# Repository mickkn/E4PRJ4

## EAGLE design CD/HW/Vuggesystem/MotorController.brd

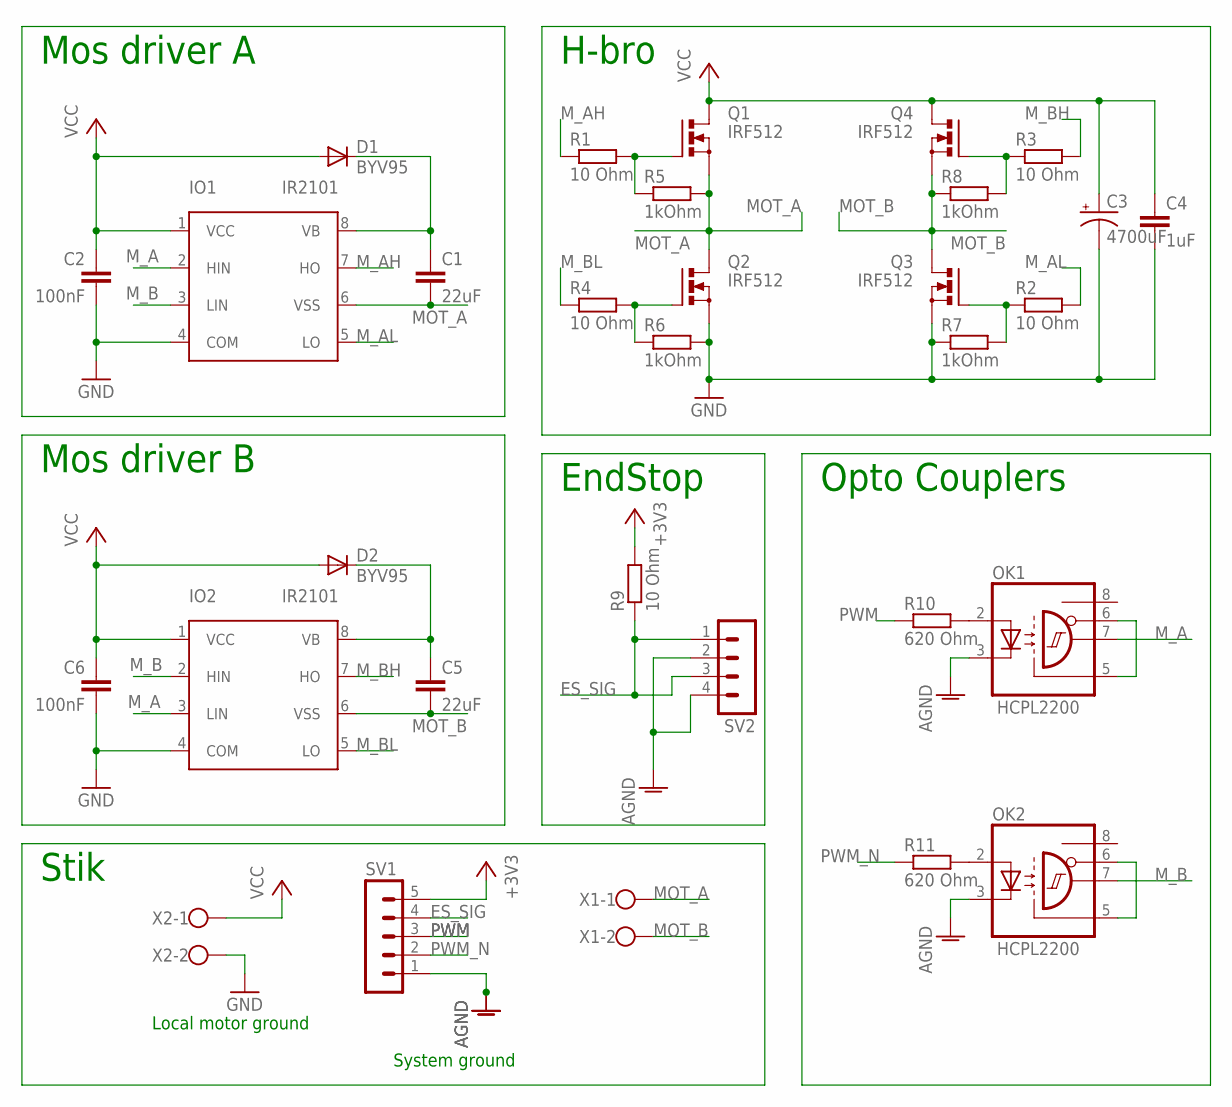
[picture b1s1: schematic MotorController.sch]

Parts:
C1, C5: 22uF; CAP-PTH-5MM
C2, C6: 100nF; CAP-PTH-5MM
C3: 4700uF; CPOL-RADIAL-1000UF-25V
C4: 1uF; CAP-PTH-5MM
D1, D2: BYV95; SOD57-10
IO1, IO2: IR2101; DIL08
OK1, OK2: HCPL2200; DIL08
Q1, Q2, Q3, Q4: IRF512; TO220BV
R1, R2, R3, R4, R9: 10 Ohm; 0207/10
R5, R6, R7, R8: 1kOhm; 0207/10
R10, R11: 620 Ohm; 0207/10
SV1: MA05-1
SV2: MA04-1
X1, X2: W237-102

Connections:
+3V3: R9.2, SV1.5
AGND: OK1.3 (C), OK2.3 (C), SV1.1, SV2.2, SV2.4
ES_SIG: R9.1, SV1.4, SV2.1, SV2.3
GND: C2.2, C3.2 (-), C4.2, C6.2, IO1.4 (COM), IO2.4 (COM), Q2.S, Q3.S, R6.2, R7.1, X2.2
MOT_A: C1.2, IO1.6 (VSS), Q1.S, Q2.D, R5.2, X1.1
MOT_B: C5.2, IO2.6 (VSS), Q3.D, Q4.S, R8.1, X1.2
M_A: IO1.2 (HIN), IO2.3 (LIN), OK1.7 (VO)
M_AH: IO1.7 (HO), R1.1
M_AL: IO1.5 (LO), R2.2
M_B: IO1.3 (LIN), IO2.2 (HIN), OK2.7 (VO)
M_BH: IO2.7 (HO), R3.2
M_BL: IO2.5 (LO), R4.1
unnamed: C5.1, D2.C, IO2.8 (VB)
unnamed: Q1.G, R1.2, R5.1
unnamed: Q2.G, R4.2, R6.1
unnamed: Q4.G, R3.1, R8.2
unnamed: Q3.G, R2.1, R7.2
unnamed: C1.1, D1.C, IO1.8 (VB)
unnamed: OK1.2 (A), R10.2
unnamed: OK2.2 (A), R11.2
unnamed: OK2.5 (GND), OK2.6 (VE)
unnamed: OK1.5 (GND), OK1.6 (VE)
PWM: R10.1, SV1.3
PWM_N: R11.1, SV1.2
VCC: C2.1, C3.1 (+), C4.1, C6.1, D1.A, D2.A, IO1.1 (VCC), IO2.1 (VCC), Q1.D, Q4.D, X2.1

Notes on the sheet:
H-bro
Mos driver A
Mos driver B
Stik
EndStop
System ground
Local motor ground
Opto Couplers

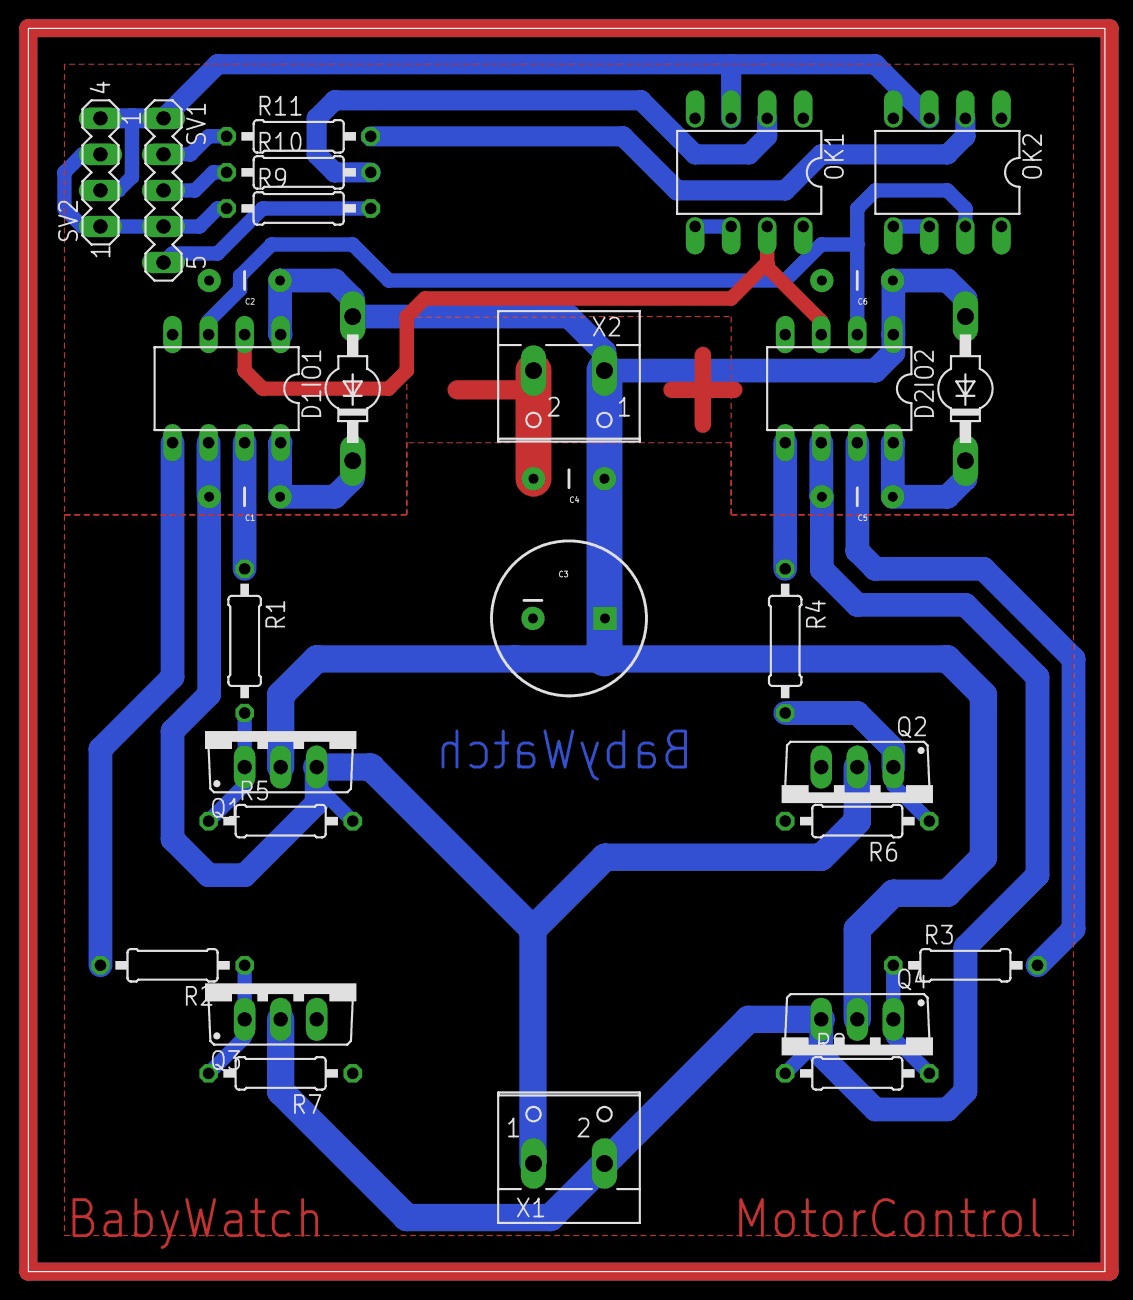
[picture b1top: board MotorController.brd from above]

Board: 2 copper layers, 75.9 x 87.6 mm, 31 parts (0 on the bottom side), 25 nets.

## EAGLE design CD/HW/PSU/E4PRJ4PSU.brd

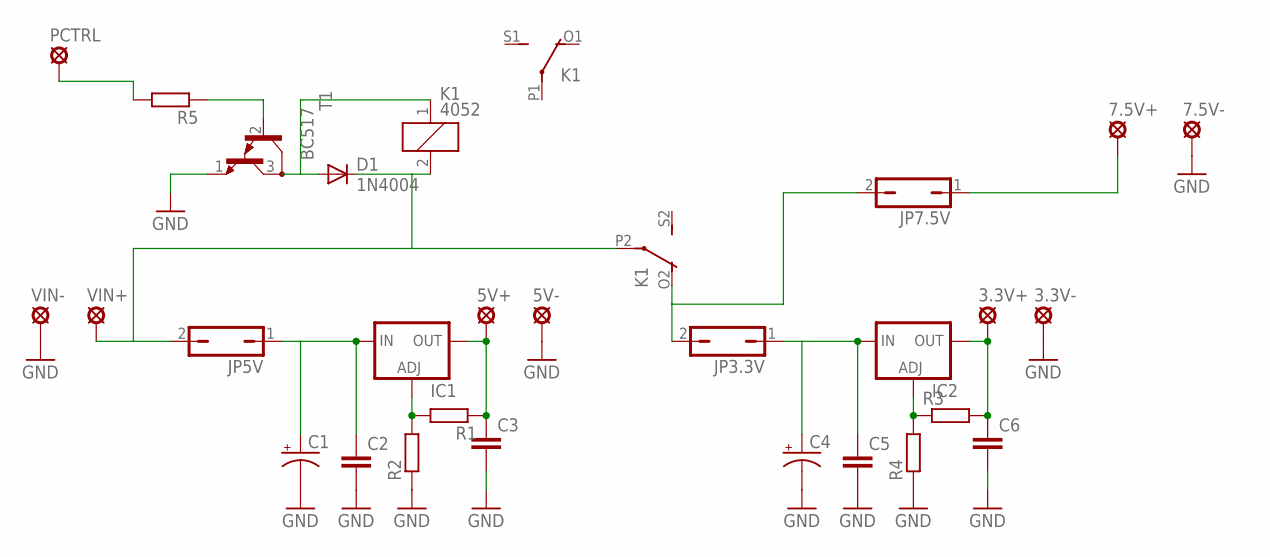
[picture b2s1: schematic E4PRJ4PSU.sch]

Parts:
3.3V+, 3.3V-, 5V+, 5V-, 7.5V+, 7.5V-: SE14
C1, C4: CPOL-USE5-10.5; E5-10,5
C2, C3, C5, C6: C-EU050-025X075; C050-025X075
D1: 1N4004; DO41-10
IC1, IC2: LM317TS; 317TS
JP3.3V, JP5V, JP7.5V: JP1Q; JP1
K1: 4052; F4052
PCTRL: SE14
R1, R2, R3, R4, R5: R-EU_0207_10; 0207/10
T1: BC517; TO92
VIN+: SE14
VIN-: SE14

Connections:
5V: JP3.3V.2, JP7.5V.2, K1.O2 (O)
GND: 3.3V-.MP, 5V-.MP, 7.5V-.MP, C1.-, C2.2, C3.2, C4.-, C5.2, C6.2, R2.1, R4.1, T1.1 (E), VIN-.MP
unnamed: C1.+, C2.1, IC1.3 (IN), JP5V.1
unnamed: 5V+.MP, C3.1, IC1.2 (OUT), R1.1
unnamed: IC1.1 (ADJ), R1.2, R2.2
unnamed: C4.+, C5.1, IC2.3 (IN), JP3.3V.1
unnamed: IC2.1 (ADJ), R3.1, R4.2
unnamed: 3.3V+.MP, C6.1, IC2.2 (OUT), R3.2
unnamed: PCTRL.MP, R5.2
unnamed: R5.1, T1.2 (B)
unnamed: D1.A, K1.1, T1.3 (C)
unnamed: D1.C, JP5V.2, K1.2, K1.P2, VIN+.MP
unnamed: 7.5V+.MP, JP7.5V.1

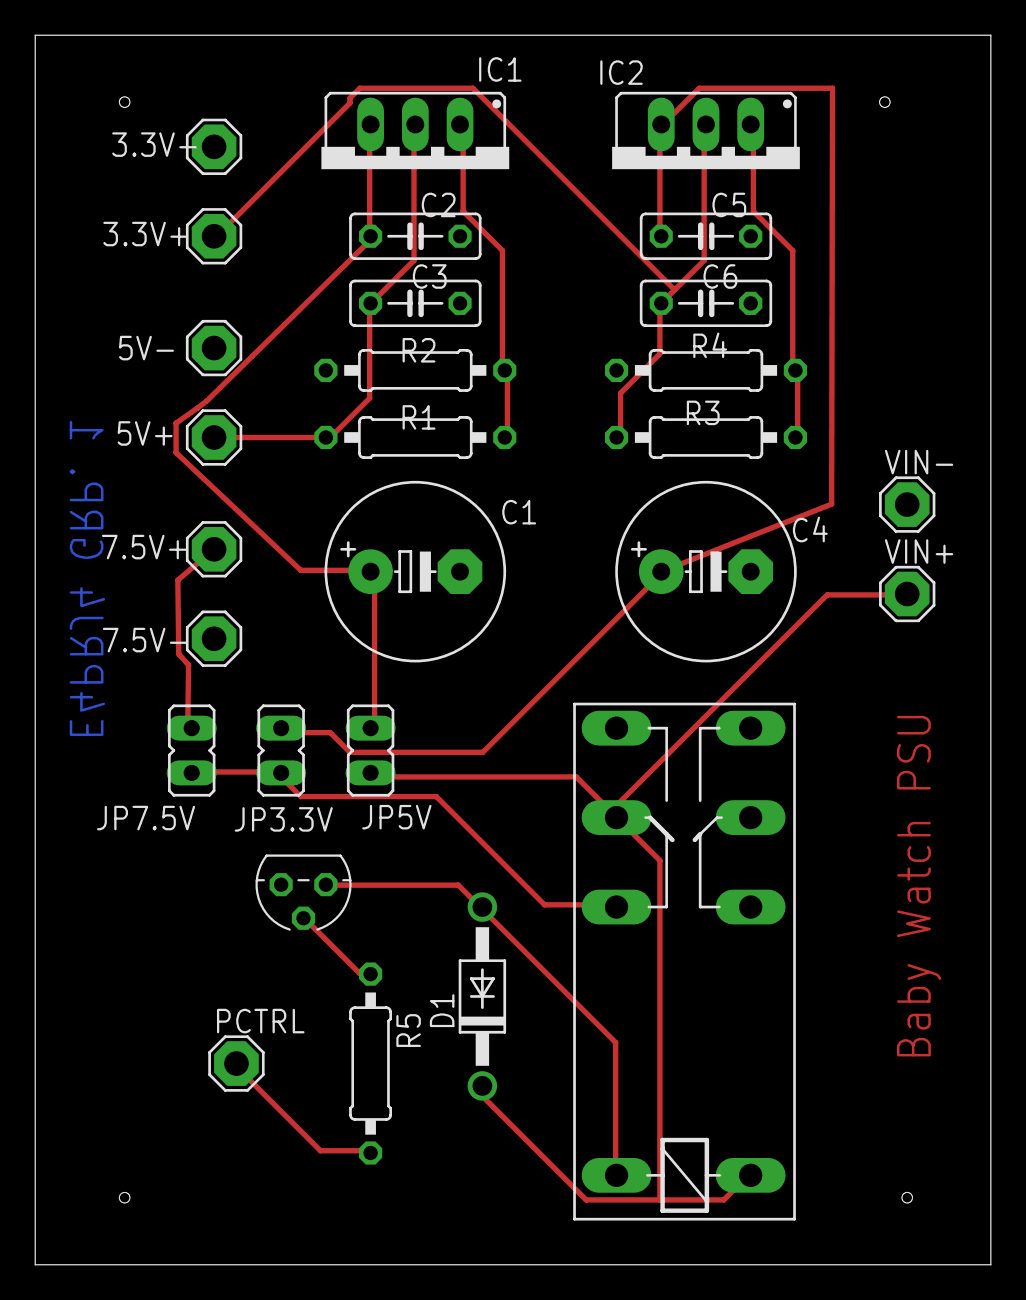
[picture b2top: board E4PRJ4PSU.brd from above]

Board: 2 copper layers, 54.3 x 69.8 mm, 28 parts (0 on the bottom side), 13 nets.

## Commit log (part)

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2015-03-05 IBD controller
2015-03-05 Overordnet IBD + start af signaltabel
2015-03-05 Overordnet IBD
2015-03-05 Kravspec rettelse efter review
2015-03-10 Intelligent lydmonitor sysark
    opdatering af systemarkitekturen for den intelligente lydmonitor
2015-03-10 Intelligent lydmonitor sysark
    Beskrivelse af IBD
2015-03-10 Intelligent lydmonitor overordnet virkemåde beskrivelse
2015-03-10 IL rettelse + indledende software ark
2015-03-10 GPIO4 -> GPIO22
    Portnummer ændret på IBD
2015-03-10 Tilføjet til signaltabel
    Tilskrift på diagram
2015-03-11 IL UML
2015-03-11 Intelligent lydmonitor sekvensdiagram
    Udkast til sekvensdiagram IL
2015-03-11 Klassediagram + Controller klasse + sh script
2015-03-11 Brugerpanel Multisim
2015-03-11 Omstrukturering...
2015-03-11 Omstrukturering... (Y)
2015-03-12 Sys ark rette med Lukas.
2015-03-12 Overordnet Domæne model
2015-03-12 Opdatering af domænemodel pdf
2015-03-12 Systemarkitektur rettelser
2015-03-12 SIgnal tabel opdateret
2015-03-12 Allokering og grænseflader
2015-03-14 Accepttest plus lidt andre rettelser
2015-03-15 UML diagram + lidt til Controller IBD
2015-03-15 Mail tekst + controller beskrivelse
2015-03-16 IL software ark diagrammer rettet
2015-03-18 IL: Mikrofondesign
2015-03-18 Vuggesys opdatering
2015-03-18 test -Felix
2015-03-18 Test
    test
2015-03-18 Mikrofon preamp design
2015-03-18 Har tilføjet signal beskriv til Vuggesystem -Felix
2015-03-20 Vuggesystem SysArk opdatering
2015-03-22 Opdatering, BDD, IBD, 2WireTTL, Kommunikationsprotokol v1.0
2015-03-24 Controller Klassediagram opdateret
2015-03-26 Klassediagram
2015-03-26 Ændring af email beskeder
    Email klasse påbegyndt
2015-03-27 IL: preamp design
2015-03-31 Yderlige opdatering af Vuggesystem SW ark
2015-03-31 IL rettelser I2C
    Rettelser iforbindelse med skift fra I2C til to signalledere
2015-03-31 Billeder af lydfiler analyse
2015-03-31 billede
2015-03-31 IL: analyse indsættelser
2015-03-31 IL: indsættelse af figurer til forundersøgelse
2015-04-02 Controller ting
    Har ucommenteret noget i intlydmonitor som fik commit til at fucke op.
    Kig evt. lige på det
2015-04-02 IL: Billeder opdateret
    Nye billeder til IL
2015-04-02 IL: Billeder opdateret endnu en gang
    Indsættelse af billeder
2015-04-03 IL: Forundersøgelse opdatering
2015-04-06 Controller ferie update
2015-04-06 Controller v2.
2015-04-06 3D tegning
2015-04-06 Revert a597f20..ae2a087
    This rolls back to commit a597f20e27cfcdca5a33b5e6a8a4413efa35adc4.
2015-04-06 Revert 4a92ae2..c3ea158
    This rolls back to commit 4a92ae2e74e7a1eef40d25d0fc7cf7e5ec6b63a3.
2015-04-06 Genrettelse af IL: forundersøgelse
2015-04-06 Efter fuckup.. Alt Controller
2015-04-07 Vuggesystem SW sysArk
2015-04-08 IL opdatering af forundersøgelse billeder
2015-04-08 IL: forundersøgelse analyser færdige
2015-04-08 IL: forundersøgelse færdig
2015-04-10 IL: Opdatering af systemtegning
2015-04-10 IL: SysArk opdatering
2015-04-10 IL: sysark SD rettelse
2015-04-10 IL: SysArk beskrivelse til SD
2015-04-10 IL: sysark UML
2015-04-10 IL: sysark diagrammer ændret
2015-04-11 VS: SW design opdatering samt HW teorisk reguleringsmodel opdatering
2015-04-12 Små rettelser
2015-04-12 felix
2015-04-14 Clean up
2015-04-15 IL: Forundersøgelse smårettelser
2015-04-15 Retterunde 1 efter review
2015-04-18 Lysintensitet + TABEL til funktionsbeskrivelser!
2015-04-18 NU MED TABEL
2015-04-18 Tabeller
2015-04-18 Overordnet rettelser
    En helt skidestak
    Grænsefladebeskrivelse til I2C har fået sin egen side :)
2015-04-19 IL: Intern review rettelser
2015-04-19 Klassediagram opdateret
    Tabel numre og beskrivelser
2015-04-20 Har flyttet motorkreds design til design -Felix
2015-04-21 IL: forundersøgelse og sysark større remake
    Alle diagrammer er opdaterede. Tekst er endnu ikke rette til
2015-04-23 Rettelser i grænseflade til I2C
2015-04-23 Controller Sekvensdiagrammer
2015-04-23 ændringer i vinkelsensor - kan ikke fuse - Felix
2015-04-23 PowerOff sekvens diagram
2015-04-23 IL: Implementering opt
2015-04-24 Controller SD rettelser
2015-04-25 Tilføjet sekvensdiagrammer til Dokumentation
2015-04-25 Forundersøgelse færdig (Praise the Lord Jesus Christ!)
2015-05-01 IL: sysark rettelser samt recbuf figur
    Sysark: kun funkbeskr. mangler
2015-05-01 Har flyttet vinkelsensor psoc projektet til google drive for at holde tingene samlet. -Felix
2015-05-06 PSU opstart
2015-05-07 Har tilføjet en fungerende vvinkelsensor - Felix
2015-05-07 IL: Systemarkitektur (DONE!)
2015-05-07 Sysark diagram færdiggørelse samt recbuf design
2015-05-08 IL: modulteststruktur samt twowirecom
2015-05-08 Modultest skabelon
2015-05-08 IL: TwoWireCom Modultest
2015-05-10 IL: Prefilter design dokumentation
2015-05-10 C: Opdatering af HTTP server
2015-05-11 har tilføjet det endelige vugge controller program. - fungerer ikke endnu
2015-05-12 5V --> 3,3 V
2015-05-12 sd - OFF
2015-05-12 Klassediagram controller
2015-05-12 PreAmp design rettelse
2015-05-12 IL schematik billeder
2015-05-13 VS: To modultests
2015-05-14 PSU PCB
2015-05-14 Controller sekvens/controller intro/sd tekst/delete Master
2015-05-14 Modultest
2015-05-14 Modultest: manStart
2015-05-14 IL: Filter opdatering
2015-05-14 VS opdatering og C implementerings opdatering
2015-05-14 har lavet print til motor kreds, og lavet lidt på motor kontrol -Felix
2015-05-14 Strøm i signaltabel opdateret
2015-05-14 Tekst til signaltabel
2015-05-14 Den store PNG til PDF konvertering
    Compile time is now shorter :D
2015-05-14 IL_ SNR_lowpass rettelse
2015-05-14 IL: spændingsregulering
2015-05-14 PSU + Arkitektur
2015-05-14 VS: Opdatering af implementering
2015-05-15 små ændringer i vuggesystem/sysark -Felix
2015-05-16 VS: Opdatering af design, implementering og modultests
2015-05-17 r tilføjet yderligere rettelser til dokumentation. -Felix
2015-05-17 VS: Opdatering af vuggeControl
2015-05-17 Implementering dokumentation - PSU
2015-05-17 EMC Rapport umiddelbart klar :)
    19 sider = 6,3 normalsider
2015-05-18 EMC Rapport - lille rettelse
2015-05-18 r fixed build fejl. slikafgift er betalt. -felix
2015-05-18 IL: RecBuf opdatering
2015-05-18 IL: Analyzer spl dokumentation
2015-05-18 IL: Modultest RecBuf
2015-05-19 Tegninger
2015-05-19 mere dokumentation -Felix
2015-05-19 Modultest - IL-test på Controller
2015-05-19 IL: Rettelser fra Arne pt. 100
2015-05-19 Billeder
2015-05-19 VS: sensorfortolker dokumentation -Felix
2015-05-19 Controller Modultest
2015-05-19 VS: Opdateret sysArk, design og implementation
2015-05-19 VS: Opdatering
2015-05-19 VS: tilføjet vinkel modultest billede-Felix
2015-05-19 SW Implementering
    Slettet bbl og blg
2015-05-19 sw imp, ik færdig
2015-05-20 PSU modultest HW
2015-05-20 Modultests PSU, Controller
2015-05-20 CD struktur + datablade
2015-05-20 SW imp + pseudokode fil
2015-05-20 IL: Dokumentation opdatering
2015-05-20 VS: Opdatering af modultests med referencer
2015-05-20 Software implementering klar til retning
2015-05-20 PSU rettelser
2015-05-20 Underskrifter i alfabetisk orden samt opsætning af RAPPORT!
2015-05-20 Fixet Bibtex så URLs også står i litteraturlisten
    Ikke vanvittig pænt
2015-05-20 BW server test billeder
2015-05-20 Diverse modultest programmer
2015-05-20 C: Modultest af website
2015-05-21 Update på rapport - samt antal anslag
2015-05-21 Controller rapport
2015-05-21 Læsevejledning og sideantalsretningslinjer
2015-05-21 Rettelser, controller-sourcekode
2015-05-21 Rapport: Arbejdsfordeling tilføjet lidt
2015-05-21 Udviklingsværktøjer + individuelle konklusioner
2015-05-21 Rettelse \iic
2015-05-21 Rapport - arbejdsproces
2015-05-21 Rapport: Baby Watch
2015-05-21 VS: Modultest af ES og MK
2015-05-22 PSU rapport done.
2015-05-22 Rapport: Baby Watch afsnit klar til review
2015-05-22 Rapport, CD
2015-05-22 Test
2015-05-22 IL: Opdatering 2.0
2015-05-22 Rapport: Indledning slået sammen med opgaveformulering
    Systembeskrivelse
2015-05-22 Systembeskrivelse
2015-05-22 IL: modultest PRE ANAL
2015-05-22 VS: Opdatering af modultest og implementering
2015-05-23 Indledning
2015-05-23 Rettelse af komplierfejl
2015-05-23 Termliste opdatering med DFT og FFT
2015-05-23 VS: Opdatering af modultest, review rettelser mm.
2015-05-23 VS: Bibtek opdatering
2015-05-23 WiFi krav og test
2015-05-23 Accepttest newpage opsætning
2015-05-23 Rapport: Krav
2015-05-23 IL: Modultest Categorizer
2015-05-23 VS: Modultest opdatering
2015-05-23 VS: tilføjet optokobler afsnit -Felix
2015-05-23 IL: Modultest Statistician
2015-05-23 IL sd rettelse
2015-05-23 IL sysark rettelser
2015-05-24 IL dokumentation af prefilter og analyzer
2015-05-24 IL prefilter modutest
2015-05-25 Rapport: Rettelser
2015-05-25 Arbejdsproces
2015-05-25 IL modultest af analyzer
2015-05-25 Babywatch og Controller rettelser
2015-05-25 VS: impl regulerings opdatering
2015-05-25 IL: Rettelser
2015-05-25 IL rettelser af kristians stuff
2015-05-25 IL_lige en sidste rettelse af kristains stuff
2015-05-25 VS: Opdatering af impl
2015-05-25 IL reference rettelser
2015-05-25 Projektrapport rettelse samt arbejdsprocess for K&L
2015-05-25 C: Opdatering af HTTP-server
2015-05-25 IL modultest endelig
2015-05-25 VS: mere reg modultest -Felix
2015-05-25 IL endelig test færdig
2015-05-25 VS: Modultest done
2015-05-26 IL filer til cd
2015-05-26 png->pdf
2015-05-26 EMC Rapport i CD, smårettelser
2015-05-26 VS: Rapport skrivning
2015-05-26 Controller kode, smårettelser
2015-05-26 Litteraturlisten er overført til Rapport
2015-05-26 VS: Dok intro skrevet
2015-05-26 Dokumentation: Indholdsfortegnelsesfix
2015-05-26 IL implementering authorer
2015-05-26 IL: ready to write!
2015-05-26 RAPPORT: afgrænsning -Felix
2015-05-26 IL: rapport forundersøgelse
2015-05-26 RAPPORT: rettelse til JH og FB arbejdsfordeling. -Felix
2015-05-26 IL sysark proj og smårettelser i sysark doku
2015-05-26 Dokumentation færdig med forbehold :)
    105 ns
2015-05-26 RAPPORT: personlig konklusion -Felix
2015-05-26 VS: Rapportskrivning
2015-05-26 Skrevet lidt til erfaringer
2015-05-26 IL: rapport opdateringer
2015-05-26 Resultater tilføjet
2015-05-26 Mødereferater i PDF
2015-05-26 RAPPORT: afgrænsning + vs
2015-05-26 IL projektrapport afsnit
2015-05-26 RAPPORT: Kristian konklusion
2015-05-26 SCRUM pdf
2015-05-26 IL: Rapport Recbuf
2015-05-26 Afgrænsningsrettelse
2015-05-26 IL: rapport opdatering
2015-05-26 VS: SW Des og impl
2015-05-26 Forside, mangler lige et fint billede
2015-05-26 RAPPORT: haha
2015-05-26 RAPPORT:
2015-05-26 Dokumentation rettet 1/3 . Til og med Controller
2015-05-26 Rettelser af dokumentation er halvejs
2015-05-27 VS: PD rettelse
2015-05-27 IL: Rettelse
2015-05-27 Opdatering
2015-05-27 Forsider
2015-05-27 VS: Dok ibd
2015-05-27 LÅST DOKUMENTATION LIGGER I GDRIVE
    For stort til Github
    Vi skal huske at inkludere det på CD
2015-05-27 RAPPORT: Fremtidig arbejde
2015-05-27 Controller konklusion
2015-05-27 Kør den ind med p
2015-05-27 Individuel konklusion
2015-05-27 RAPPORT: nyt resumé -Felix
2015-05-27 rapport: Erfaringer opdatering
2015-05-27 IL: Rapport henvisninger til dokumentation
2015-05-27 RAPPORT: review af erfaringsafsnit.
2015-05-27 RAPPORT: resume rettelse -Felix
2015-05-27 Resumé andet review
2015-05-27 VS kode og datasheet
2015-05-27 RAPPORT: Indledning rettet
2015-05-27 arbejdsproces 1. review
2015-05-27 RAPPORT: ordner bilags CD
2015-05-27 Fremtidigt arbejde
2015-05-27 RAPPORT: review resultater og udviklingsværktøjer
2015-05-27 Rapport: krav review
2015-05-27 RAPPORT: tilføjet abstract -Felix
2015-05-27 RAPPORT: rettet indv. konklision -Felix
2015-05-27 RAPPORT: reveiw af babywatch -Felix
2015-05-27 rapport IL rettelser - ready to review!
2015-05-27 Lidt vuggesystem, Hofni retter selv færdig
2015-05-27 RAPPORT: Review af PSU
2015-05-27 Erfaringer reviewet
2015-05-27 rapport: resume, abstrac, projektafgræn
2015-05-27 indi. konklusion
2015-05-27 indivuelle konklusioner
2015-05-27 VS bilag
2015-05-27 rapport resultater
2015-05-27 RAPPORT: konklusion klar til review -Felix
2015-05-27 Første review af resultater
2015-05-27 motorkreds datablade tilføjet -Felix
2015-05-27 RAPPORT: første rettelser
2015-05-27 Rapport rettelser
2015-05-27 Opdatering af resulater
2015-05-27 fedt
2015-05-27 Barbering af IL og C

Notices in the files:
parts and their libraries:
SparkFun-Passives: Licensing: Creative Commons ShareAlike 4.0 International - https://creativecommons.org/licenses/by-sa/4.0
